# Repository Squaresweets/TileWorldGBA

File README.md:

# TileWorldGBA

[</a>](https://twitter.com/SqSweetsGames)
[</a>](https://forthebadge.com)

# Tileworld has now been shutdown, so this whole project is sorta dead lol. I'm still very proud of it.

# What and why
Basically, I wanted to port something to the Gameboy Advance, and I thought it would be kinda funny to make a cross platform multiplayer game since it hadn't been done before. The perfect candidete for this was [TileWorld](https://tileworld.org) since I had worked on the mobile port and it is a pretty simple game. This whole thing has taken a long time, partially due to exams and partially due to lots of problem solving.

For playing this you have two options, either using a normal pico connected to your computer using the stuff found in the Python folder, or using the custom firmware to do it all just on a Pico W.

Latest video about the project can be found [here](https://www.youtube.com/watch?v=uGY5kjLEVD8)

Using this project requires [this adapter](https://stacksmashing.gumroad.com/l/gb-link)!

# Development checklist
- Physics ✔️
- Server -> Python communicaiton ✔️
- Python -> GBA communication ✔️
- Multiboot (Hard) ✔️
- Spawn loading ✔️
- Location information sending ✔️
- Loading screen ✔️
- Receiving tile places ✔️
- New chunks loading ✔️
- Changing tiles ✔️
- Other players ✔️
- Map system ✔️
- Coordinate system ✔️
- Wireless
  - TLS ✔️
  - Custom WS client ✔️
  - Downloading ROM from github ✔️
  - UF2 editor to add wifi SSID and password
  - Sending data via PIO
  - Multiboot
- 3D printed game holder, and potentially a custom PCB
  - Box ✔️
  - Schematic ✔️
  - PCB ✔️
  - Case

# Notes
The collision system used is a port of [this](https://github.com/dfranx/Colly) system by the creator of TileWorld.

Also, I just wanted to put it out there that this is my first C project, and my first GBA game, so none of this is particularly optimised or neat. This is a passion project and was done completly for fun and to learn C, so feedback is always appreciated!

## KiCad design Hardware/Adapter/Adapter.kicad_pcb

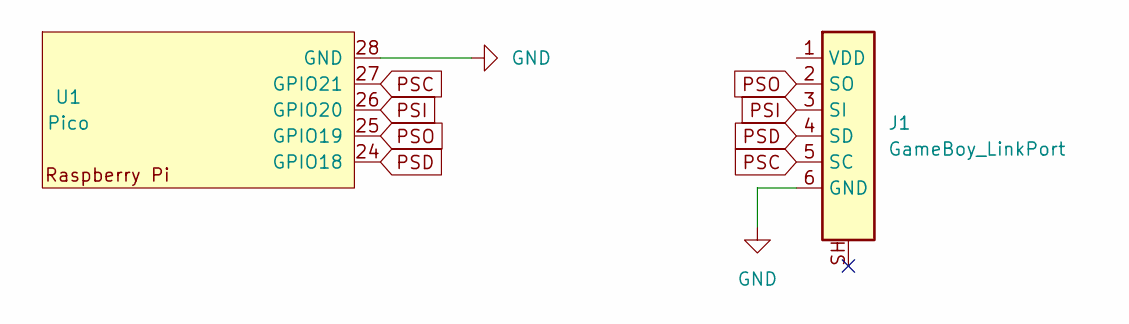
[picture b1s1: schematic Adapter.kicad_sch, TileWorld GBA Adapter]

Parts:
J1: GameBoy_LinkPort; GameBoy_LinkPort_MGB_Horizontal
U1: Pico; RPi_Pico_SMD_TH

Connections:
GND: J1.6 (GND), U1.28 (GND)
PSC: J1.5 (SC), U1.27 (GPIO21)
PSD: J1.4 (SD), U1.24 (GPIO18)
PSI: J1.3 (SI), U1.26 (GPIO20)
PSO: J1.2 (SO), U1.25 (GPIO19)

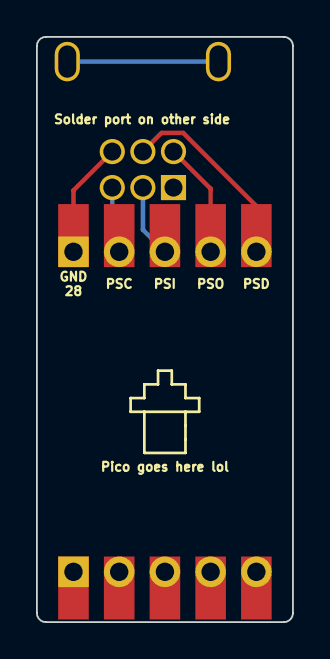
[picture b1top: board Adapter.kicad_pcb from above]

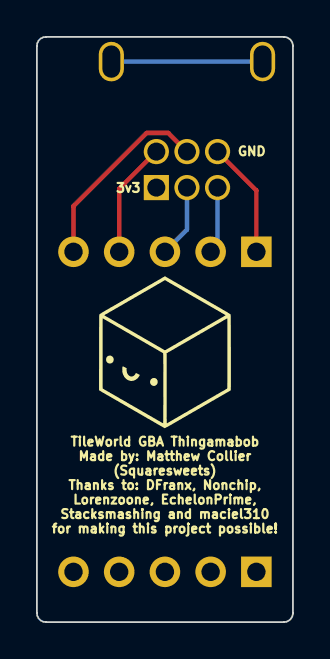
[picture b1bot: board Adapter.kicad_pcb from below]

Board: 2 copper layers, 14.2 x 32.5 mm, 3 parts (2 on the bottom side), 5 nets.

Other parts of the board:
G1: LOGO; SSG Logo

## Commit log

2022-02-01 Made a simple map
2022-02-02 More stuff, made house, started trying to get sprites to work, failed
2022-02-05 Put the player sprite in the middle of the screen
    Now to make it so the player moves and the camera follows
2022-02-06 Camera now tracks player
2022-02-07 Camera system, now to do physics, shouldn't be too hard, right?
2022-02-14 Started on physics stuff
2022-02-15 collisions working, need to be optimised (alot)
2022-03-18 Starting on fixed point stuff
    Removed some old stuff to test, have the same camera movement but with no floats in sight!
2022-03-19 Trying to make collision fixed point, almost works, doesn't actually work yet
2022-03-20 No floats left, woo
2022-03-20 Started on physics, does not yet work
    Also need to optimise everything, like really optimise everything, gonna be fun
2022-03-21 Better, still not working
2022-03-22 I'm stupid
    Apparently when I removed all floating stuff I still kept in * 0.25 (and some other stuff) which obviously is still floating
2022-03-22 Physics working, will now see if I can do data transfer stuff (actually I might do optimisations first)
2022-03-22 Ladders + stuff loops round
2022-03-23 Added game cart graphic
2022-03-23 Added game cart
2022-03-23 Gamecart
2022-03-23 Added gamecart
    Cor that took a lot of commits
2022-03-24 Started on doing SIO stuff
    At the moment it is working, but just sending 0x65 (Why? Cause it is a nice number)
    Next I need to do python stuff
2022-03-25 Now using tonc stuff better (english good)
2022-03-25 More SIO stuff
2022-03-26 More stuff, didn't work, might look at getting a text engine working for debugging
2022-03-28 More sio stuff, doesn't work
2022-03-28 Ok all working! Now to get multi-boot working
2022-04-06 Starting doing multiboot stuff
    Seems pretty fun, basically just converting https://github.com/maciel310/gba-mmo-proxy/blob/main/multiboot.c into python, and questioning some strange coding choices from the c version
2022-04-07 More work, but no working
    Such is the life of a coder
2022-04-08 Backup before changes
    Optimisations time
2022-04-09 Multi-boot working
2022-04-11 Now sends a LOT faster, many thanks to maciel310 for the help!
2022-04-12 Started on ws stuff
2022-04-13 Getting tile data correctly from ws
    Also spent today working on a possible case for the adapter and raspberry pi zero w
2022-04-14 Tried to solve transmission errors, failed, gn
2022-04-18 Worked on logic for recieving stuff in python from gba, not tested
2022-04-20 More work, started on logic for python->gba
    There are going to be less commits now due to exams, wooo
2022-04-24 More work on SIO stuff, none of it tested
    Loving exams
2022-04-26 Now connecting to tileworld, just gotta get my head around pointers and I can start sending other stuff
2022-04-27 Slightly more work on how to send stuff
    Now to have to use floats because that's what tileworld uses, NOOOOOOOOOOO!!!!!
2022-04-28 Added development checklist to readme
2022-04-29 God this map stuff is going to be FUN
    If only exams didn't take up so much of my time and I didn't constantly get distracted by youtube
2022-05-01 Loads more work on map stuff
    Some problems with receiving data from websocket, will look at fixing
2022-05-02 I'm trying here, this websocket stuff is really annoying
2022-05-03 Serial is technically working rn, but would be much better to use "on_message" as checking for a message each frame is very slow
2022-05-04 WS stuff should be working now :D
2022-05-04 Lots more work on trying to get map loading
2022-05-05 Map is now loading on gba
2022-05-06 Honestly not much changed at all
    I went on a run, so I didn't have time to code lol
2022-05-07 Not much, had to revise a bunch for upcoming exams
    Started on functions and logics to load chunks
2022-05-08 Seamless map loading not yet working
2022-05-09 Have eliminated the loadChunks function from being the problem
    The problem also seems to be pretty intermittent, which is a problem.
    I have a german speaking exam tomorrow, wish me luck
2022-05-11 Found the bug
    Looks like the interupt is getting called in the middle of loading new chunks which messes stuff up, but ive gotta fix it tomorrow
2022-05-13 Fixed the bug, something do do with interrupts
2022-05-14 Not much work, got me first exam in a couple of days so lots of revision
2022-05-15 Spawn chunks can now be explored
    Took me a while due to annoying bugs
2022-05-15 Set up the groundwork for sending data to the server
    Pretty messy code, will try and improve it
2022-05-29 Trying to do player movement
    Sorry for break, had exams
2022-05-30 I am confused
2022-05-31 Player movement working... kinda
    Very jittery still
2022-06-03 Fixed player movement, added a loading screen
    Although the new code is "fancier" it is way worse, will fix it tomorrow
2022-06-04 Going to make the loading screen nicer
2022-06-04 More work on loading screen
    This code is horrible, I am so sorry
2022-06-05 A lot of work, loading screen, faster sending by changing the firmware, starting on receiving place commands
    I'm sleeping now
2022-06-06 Trying to receive tile places
2022-06-08 I can't work this out
    fun
2022-06-16 You can now place tiles and it goes on the GBA
    Still a bit iffy tho
2022-06-17 Placing tiles now works!
2022-06-17 Going to start formating this a bit better with the map stuff
    But imma do that tomorrow, it is soooo hot today, got up to 33, ugh, not coding weather
2022-06-18 Put map stuff in a separate document to sio
    Also started on some plans for loading new chunks
2022-06-21 Improved multiboot a bunch
    :D
2022-06-21 Changing a bit of code, not much, just making multiboot nicer
    Imma work on loading new chunks soon
2022-06-22 Looking into a few errors you get from data transmission after a while of it running
    I will start doing chunk loading at some point I swear.
    Also, final exam tomorrow!
2022-06-23 Working on loading new chunks
2022-06-24 Requesting new chunks working
2022-06-25 Am now considering re writing a bunch of SIO stuff to make the interrupt stuff as short as possible
2022-06-25 Started reformatting stuff so less is in the interupt, this will take a while
2022-06-26 quicksave
2022-06-28 Stuff is now threadsafe
2022-06-28 Chunk loading now working
2022-06-28 Started workin on placing tiles
2022-06-30 attempt to optimise
2022-06-30 Lags less, but because of that it isn't fast enough to load new chunks
2022-07-01 Tweaks
2022-07-04 Working on placing tiles
2022-07-05 Tile placements now functional
    Also this is my 100th commit, so that is exciting.
    Pretty much all of the functionality I wanted to add has been added, though I may look at adding other players, that would just be pretty intensive and hard.
    Next I really want to get it running wirelessly on the new raspberry pi pico W, so it wouldn't have to be tethered to python, fun fun fun
2022-07-05 Confine camera to screen when loading and optimised
2022-07-08 Tweaks getting ready to do pico W stuff
2022-07-10 Connecting to Tileworld server, or at least upgrading to WSS
2022-07-11 Working on porting WS
2022-07-12 idk what the bug was but I fixed it
2022-07-17 I have ideas
2022-07-20 Pain
2022-07-22 https://docs.google.com/document/d/1c4j_fxBn_UVRCnMS082wecn5pVlA4KfM2oogZBTVXSc/edit?usp=sharing
2022-07-24 TCP stuff testing
2022-07-25 Stuff is now actually kinda working
2022-07-26 Attempting to get gitignore to work
2022-07-26 Stuff is actually kinda working now!
2022-07-26 Working on box art
2022-07-27 Planning to do sio stuff
2022-07-28 Working on receiving player movement
2022-07-29 Added debug stuff and some work on other players
2022-07-29 Next up, fixing some syncing problems with the map
2022-08-05 Realised syncing issues were related to clicking on and off of python. Work on firmware, big buffer and ideas for multiboot
2022-08-06 Work on downloading .gba file from github
2022-08-08 Now downloading the game from github
2022-08-09 Multiboot work, none tested
2022-08-10 Working on a minimap (not working yet)
2022-08-11 Work on minimap, close to working now
2022-08-11 Map system seems to be functioning, but still has a couple of things in terms of hiding other sprites
    This whole thing has uncovered some problems with my chunk loading system which I gotta fix
2022-08-12 Work on minimap, lots more problems uncovered
    Still problems with chunk loading during elevator aswell as player sprite disapearing when too far away from spawn.
    Also gotta look at other sprites appearing ontop of minimap, though should be a reasonably simple fix
2022-08-13 More work and stuff lol, being too far away from spawn breaks stuff
2022-08-14 Soon will have a spinnin gif of game box
2022-08-14 Added gif
2022-08-14 This whole business with preventing syncing issues is really annoying and I can't get my head around it
2022-08-15 Fixed some bugs and started looking at text system
2022-08-16 What on earth is this text system
2022-08-17 GBA ROM is pretty much done now, whoop! Now to *MAYBE* look at pcb design, or wait until I start electronics at college
2022-08-18 Trying to learn KICAD
2022-08-19 Work on adapter and changed some camera settings
2022-08-21 More work on adapter
2022-08-22 Not much work at all tbh, trying and failing to import to blender
2022-08-24 More adapter work
2022-08-29 Backup before remaking adapter pcb
2022-08-29 try stuff lol
    The official name of the adapter is now the TileWorld GBA thingamabob, don't @ me
2022-08-30 Redid adapter, almost done, but I just wanna code stuff now
2022-08-31 Hardware almost done
    Making it soon, but also I need to do more pico firmware stuff
2022-09-01 Firmware is pretty much done now I think
2022-09-02 ok almost done now
2022-09-02 Updated boxart to fix spelling mistake
2022-09-04 working on getting a system to be able to drag config file into pico
2022-09-05 cannot get print to work when using usb
2022-09-06 Debug output is working now, finally
2022-09-08 Work on FAT stuff
    Stuff is going slowly due to college
2022-09-11 Not much work
2022-09-12 gitignore
2022-09-19 looking for another way to add config stuff
2022-09-20 Work on uf2 editor
2022-09-22 Flash stuff is working now, now to add stuff to let you add in wifi password and stuff
2022-09-23 Removed venv
2022-09-25 Gonna start working on this patcher in a seperate respotitory
2022-10-03 Removed some otehr stuff
2022-10-05 SSID STUFFF
2022-10-06 Finished ssid stuff
2024-02-07 rip tileworld
